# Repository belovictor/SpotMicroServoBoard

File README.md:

# SpotMicroServoBoard

SpotMicro 6 servo PWM board with voltage/current measurement

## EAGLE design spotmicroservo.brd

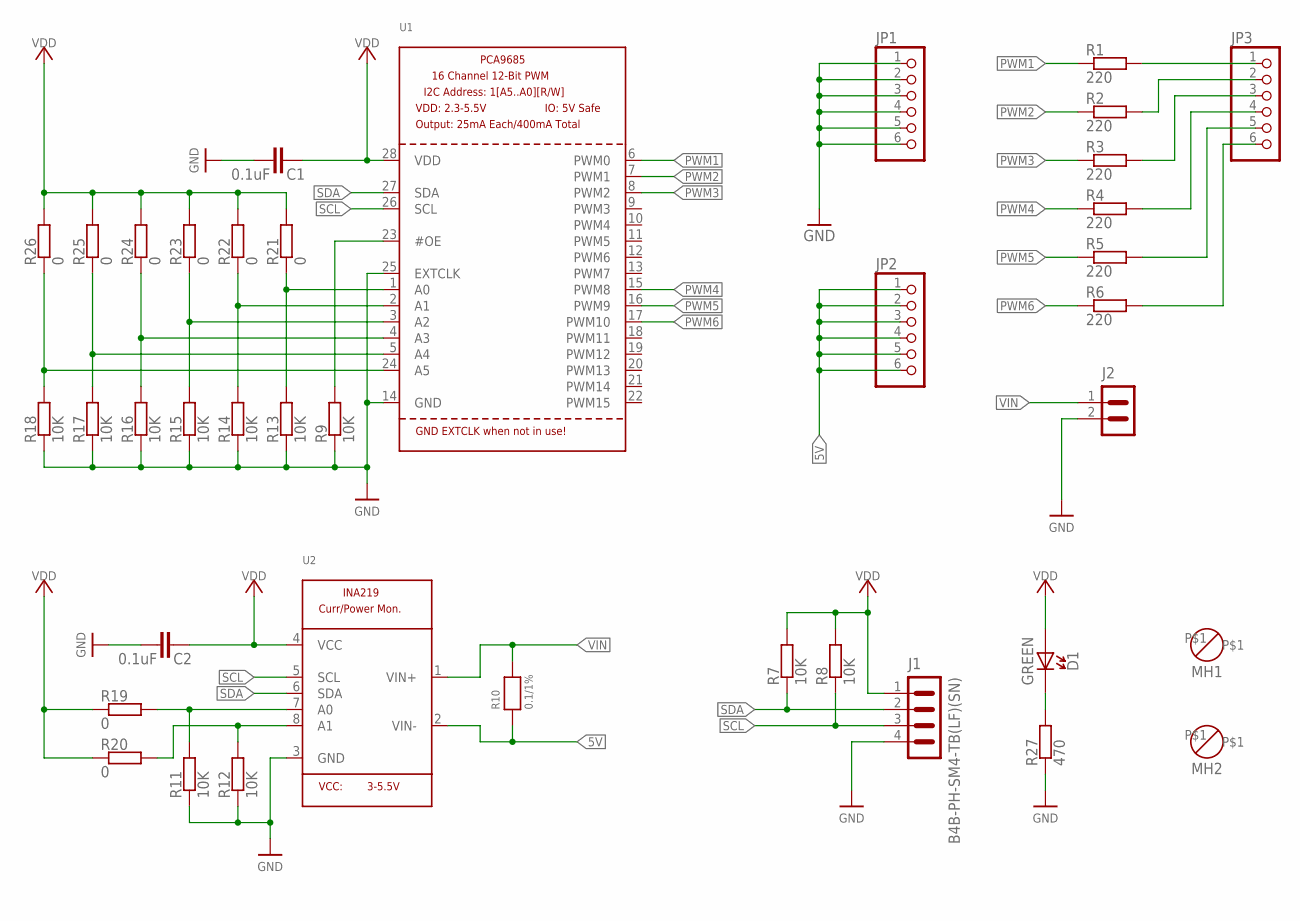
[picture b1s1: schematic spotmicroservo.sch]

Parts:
C1, C2: 0.1uF; C0402
D1: GREEN; D0402
J1: B4B-PH-SM4-TB(LF)(SN); CON_JST_B4B-PH-SM4-TB(LF)(SN)
J2: CON_HEADER_1X02-B2B-XH-A(LF)(SN); JST_B2B-XH-A(LF)(SN)
JP1, JP2, JP3: PINHD-1X6B; 1X06-BIG
MH1, MH2: MOUNT-HOLE2.6MM; MOUNT-HOLE2.6
R1, R2, R3, R4, R5, R6: 220; R0402
R7, R8, R9, R11, R12, R13, R14, R15, R16, R17, R18: 10K; R0402
R10: 0.1/1%; MICROBUILDER_2512
R19, R20, R21, R22, R23, R24, R25, R26: 0; R0402
R27: 470; R0402
U1: PCA9685; TSSOP28
U2: MICROBUILDER_INA219; MICROBUILDER_SOT23-8

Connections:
5V: JP2.1, JP2.2, JP2.3, JP2.4, JP2.5, JP2.6, R10.1, U2.2 (VIN-)
GND: C1.1, C2.1, J1.4, J2.2, JP1.1, JP1.2, JP1.3, JP1.4, JP1.5, JP1.6, R9.1, R11.1, R12.1, R13.1, R14.1, R15.1, R16.1, R17.1, R18.1, R27.1, U1.14 (GND), U1.25 (EXTCLK), U2.3 (GND)
unnamed: JP3.1, R1.2
unnamed: R9.2, U1.23 (#OE)
unnamed: JP3.2, R2.2
unnamed: JP3.3, R3.2
unnamed: JP3.4, R4.2
unnamed: JP3.5, R5.2
unnamed: JP3.6, R6.2
unnamed: R11.2, R19.2, U2.7 (A0)
unnamed: R12.2, R20.2, U2.8 (A1)
unnamed: R13.2, R21.1, U1.1 (A0)
unnamed: R14.2, R22.1, U1.2 (A1)
unnamed: R15.2, R23.1, U1.3 (A2)
unnamed: R16.2, R24.1, U1.4 (A3)
unnamed: R17.2, R25.1, U1.5 (A4)
unnamed: R18.2, R26.1, U1.24 (A5)
unnamed: D1.2 (C), R27.2
PWM1: R1.1, U1.6 (PWM0)
PWM2: R2.1, U1.7 (PWM1)
PWM3: R3.1, U1.8 (PWM2)
PWM4: R4.1, U1.15 (PWM8)
PWM5: R5.1, U1.16 (PWM9)
PWM6: R6.1, U1.17 (PWM10)
SCL: J1.3, R8.1, U1.26 (SCL), U2.5 (SCL)
SDA: J1.2, R7.1, U1.27 (SDA), U2.6 (SDA)
VDD: C1.2, C2.2, D1.1 (A), J1.1, R7.2, R8.2, R19.1, R20.1, R21.2, R22.2, R23.2, R24.2, R25.2, R26.2, U1.28 (VDD), U2.4 (VCC)
VIN: J2.1, R10.2, U2.1 (VIN+)

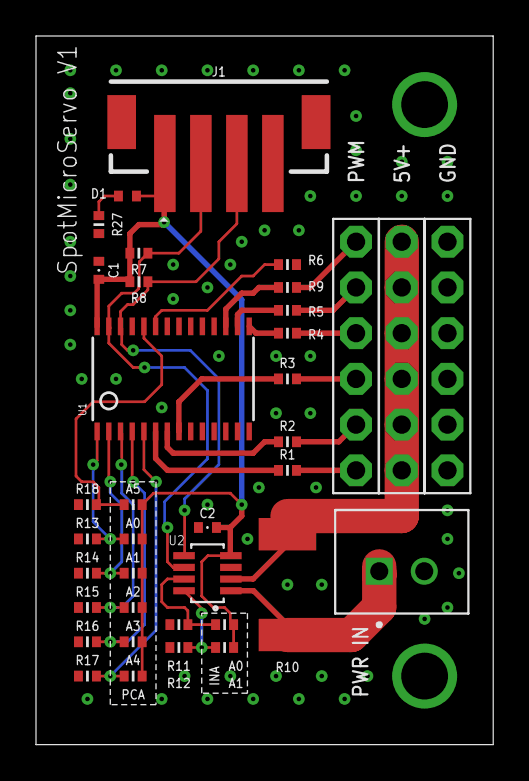
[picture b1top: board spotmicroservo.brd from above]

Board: 2 copper layers, 25.4 x 39.4 mm, 39 parts (0 on the bottom side), 28 nets.

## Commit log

2022-02-06 Fix power path
2022-02-06 Add ground plane shapes
2022-02-07 Smaller vias. Prettify power path.
